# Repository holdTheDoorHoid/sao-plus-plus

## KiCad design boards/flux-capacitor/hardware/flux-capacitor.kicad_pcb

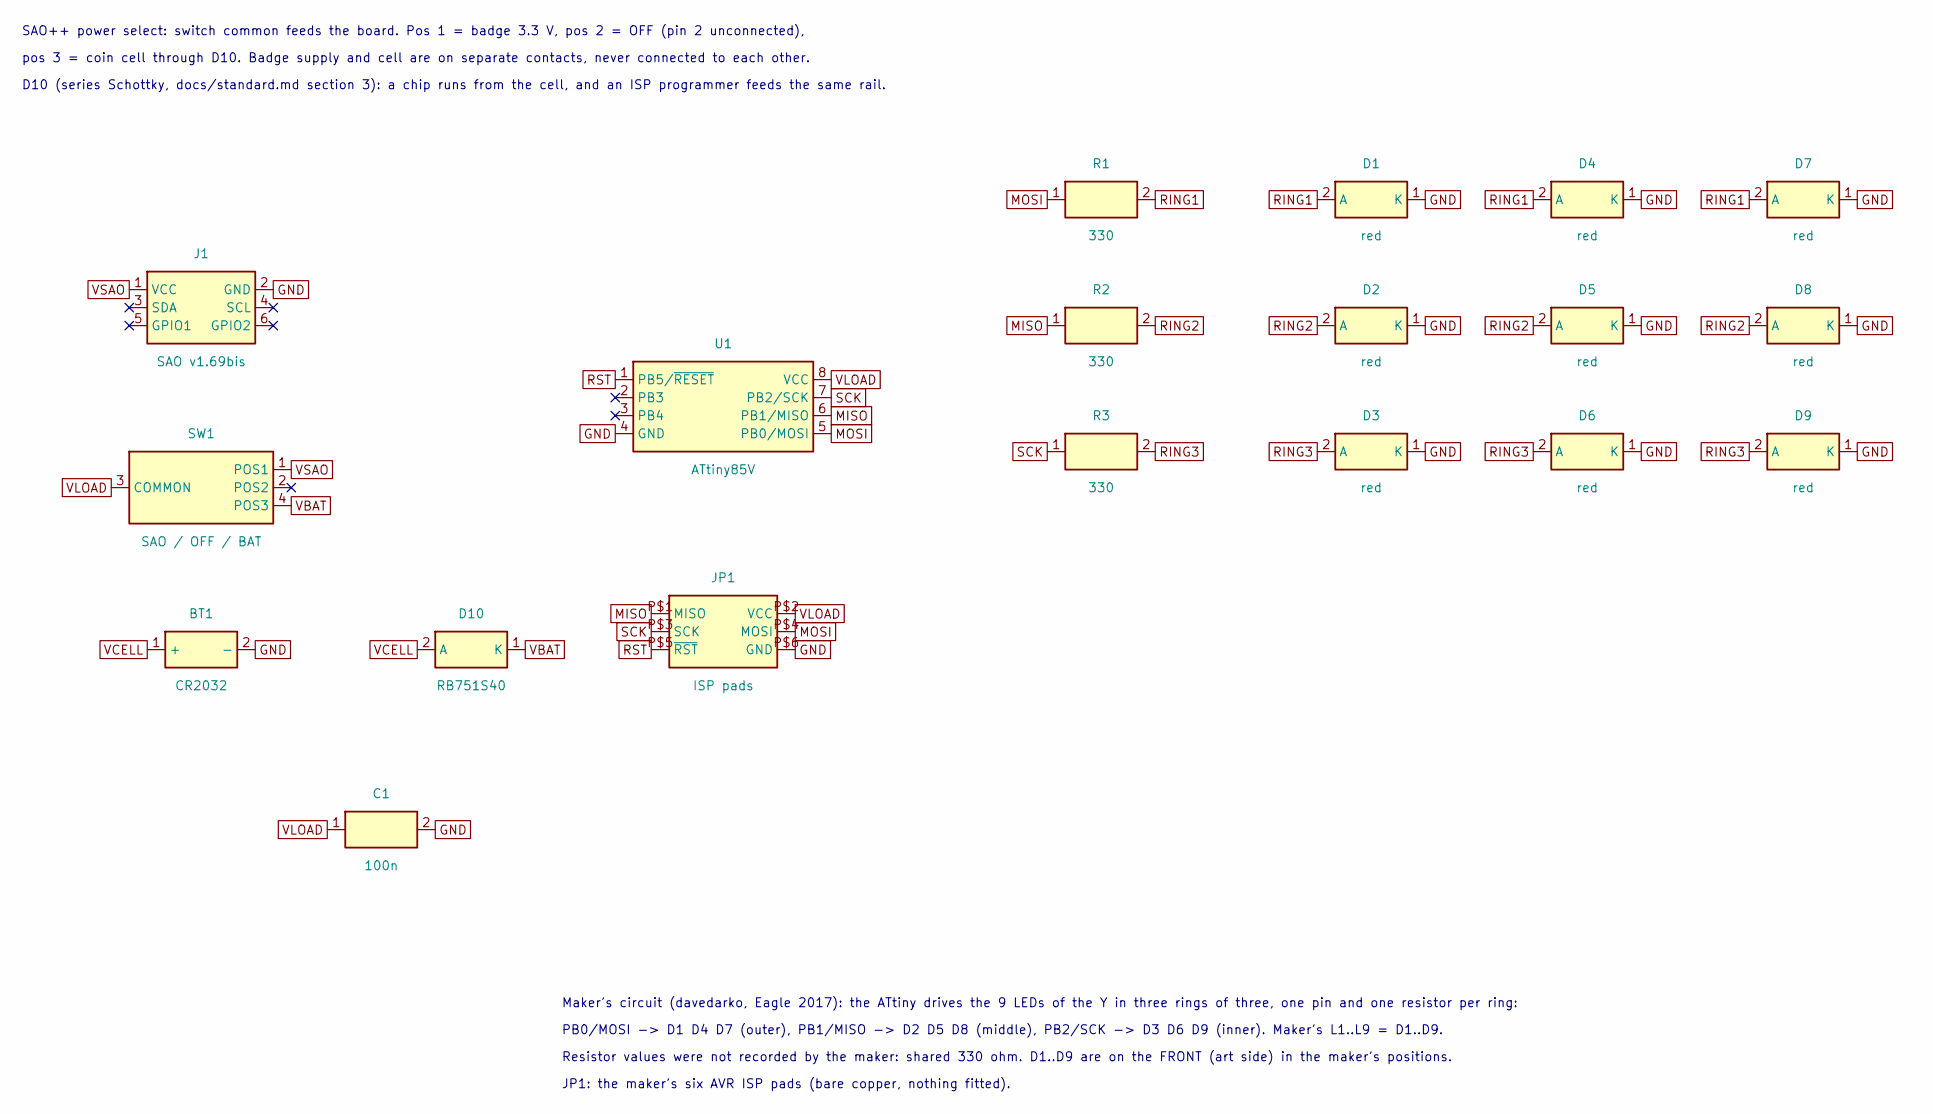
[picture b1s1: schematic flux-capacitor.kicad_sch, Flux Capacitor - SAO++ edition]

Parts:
BT1: CR2032; SAOPP_BAT-01_CR2032_SMD_TE_BAT-HLD-001; MPN BAT-HLD-001; LCSC C7501066
C1: 100n; SAOPP_C_0603_1608Metric; MPN CC0603KRX7R9BB104; LCSC C14663
D1, D2, D3, D4, D5, D6, D7, D8, D9: red; LED_1206_3216Metric; MPN LTST-C150KRKT; LCSC C125086
D10: RB751S40; D_SOD-523; MPN RB751S40T1G; LCSC C232576
J1: SAO v1.69bis; SAOPP_CONN-01_BoxHeader_2x03_P2.54mm_SMD_XFCN_BH254VS-6P; MPN BH254VS-6P; LCSC C492445
JP1: ISP pads; 2X3_SMD_PAD; MPN none: bare pads, nothing fitted
R1, R2, R3: 330; SAOPP_R_0603_1608Metric; MPN 0603WAF3300T5E; LCSC C23138
SW1: SAO / OFF / BAT; SAOPP_SW-01_Slide_SP3T_CK_PCM13SMTR; MPN PCM13SMTR; LCSC C221842
U1: ATtiny85V; SO08-EIAJ; MPN ATTINY85V-10SU; LCSC C152192

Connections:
GND: BT1.2 (-), C1.2, D1.1 (K), D2.1 (K), D3.1 (K), D4.1 (K), D5.1 (K), D6.1 (K), D7.1 (K), D8.1 (K), D9.1 (K), J1.2 (GND), JP1.P$6 (GND), U1.4 (GND)
MISO: JP1.P$1 (MISO), R2.1, U1.6 (PB1/MISO)
MOSI: JP1.P$4 (MOSI), R1.1, U1.5 (PB0/MOSI)
RING1: D1.2 (A), D4.2 (A), D7.2 (A), R1.2
RING2: D2.2 (A), D5.2 (A), D8.2 (A), R2.2
RING3: D3.2 (A), D6.2 (A), D9.2 (A), R3.2
RST: JP1.P$5 (~RST), U1.1 (PB5/~RESET)
SCK: JP1.P$3 (SCK), R3.1, U1.7 (PB2/SCK)
VBAT: D10.1 (K), SW1.4 (POS3)
VCELL: BT1.1 (+), D10.2 (A)
VLOAD: C1.1, JP1.P$2 (VCC), SW1.3 (COMMON), U1.8 (VCC)
VSAO: J1.1 (VCC), SW1.1 (POS1)

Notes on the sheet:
SAO++ power select: switch common feeds the board. Pos 1 = badge 3.3 V, pos 2 = OFF (pin 2 unconnected),
pos 3 = coin cell through D10. Badge supply and cell are on separate contacts, never connected to each other.
D10 (series Schottky, docs/standard.md section 3): a chip runs from the cell, and an ISP programmer feeds the same rail.
Maker's circuit (davedarko, Eagle 2017): the ATtiny drives the 9 LEDs of the Y in three rings of three, one pin and one resistor per ring:
PB0/MOSI -> D1 D4 D7 (outer), PB1/MISO -> D2 D5 D8 (middle), PB2/SCK -> D3 D6 D9 (inner). Maker's L1..L9 = D1..D9.
Resistor values were not recorded by the maker: shared 330 ohm. D1..D9 are on the FRONT (art side) in the maker's positions.
JP1: the maker's six AVR ISP pads (bare copper, nothing fitted).

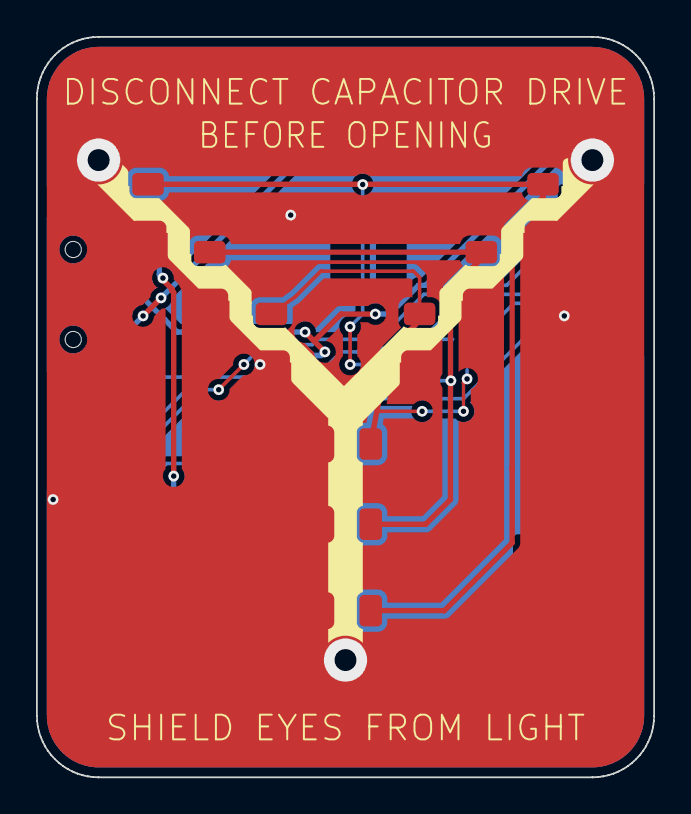
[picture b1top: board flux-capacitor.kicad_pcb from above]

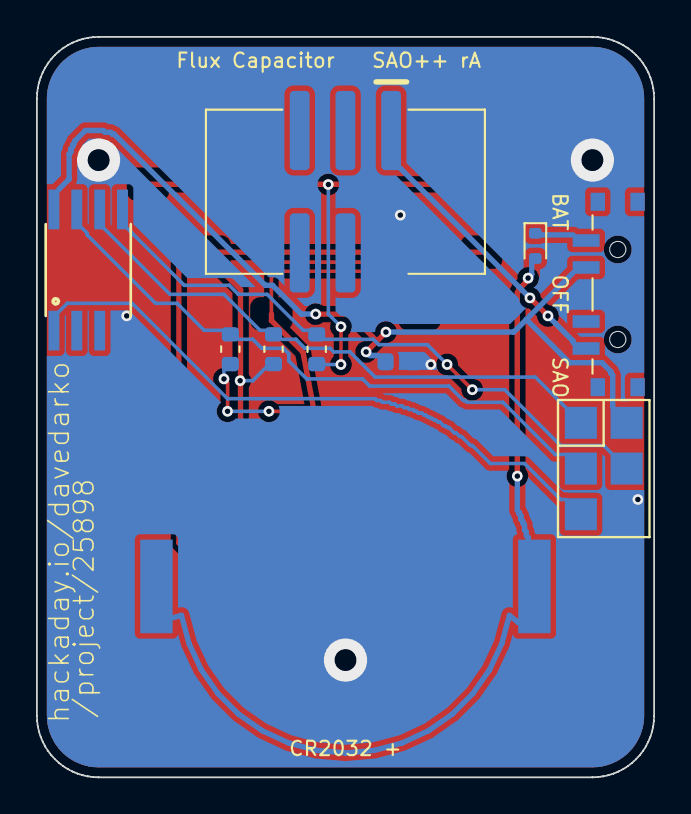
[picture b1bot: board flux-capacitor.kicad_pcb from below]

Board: 2 copper layers, 34.3 x 41.1 mm, 19 parts (10 on the bottom side), 12 nets.

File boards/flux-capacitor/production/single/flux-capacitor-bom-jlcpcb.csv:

Comment,Designator,Footprint,LCSC Part #
CR2032,BT1,SAOPP_BAT-01_CR2032_SMD_TE_BAT-HLD-001,C7501066
100n,C1,SAOPP_C_0603_1608Metric,C14663
red,"D1,D2,D3,D4,D5,D6,D7,D8,D9",LED_1206_3216Metric,C125086
RB751S40,D10,D_SOD-523,C232576
SAO v1.69bis,J1,SAOPP_CONN-01_BoxHeader_2x03_P2.54mm_SMD_XFCN_BH254VS-6P,C492445
ISP pads,JP1,2X3_SMD_PAD,
330,"R1,R2,R3",SAOPP_R_0603_1608Metric,C23138
SAO / OFF / BAT,SW1,SAOPP_SW-01_Slide_SP3T_CK_PCM13SMTR,C221842
ATtiny85V,U1,SO08-EIAJ,C152192

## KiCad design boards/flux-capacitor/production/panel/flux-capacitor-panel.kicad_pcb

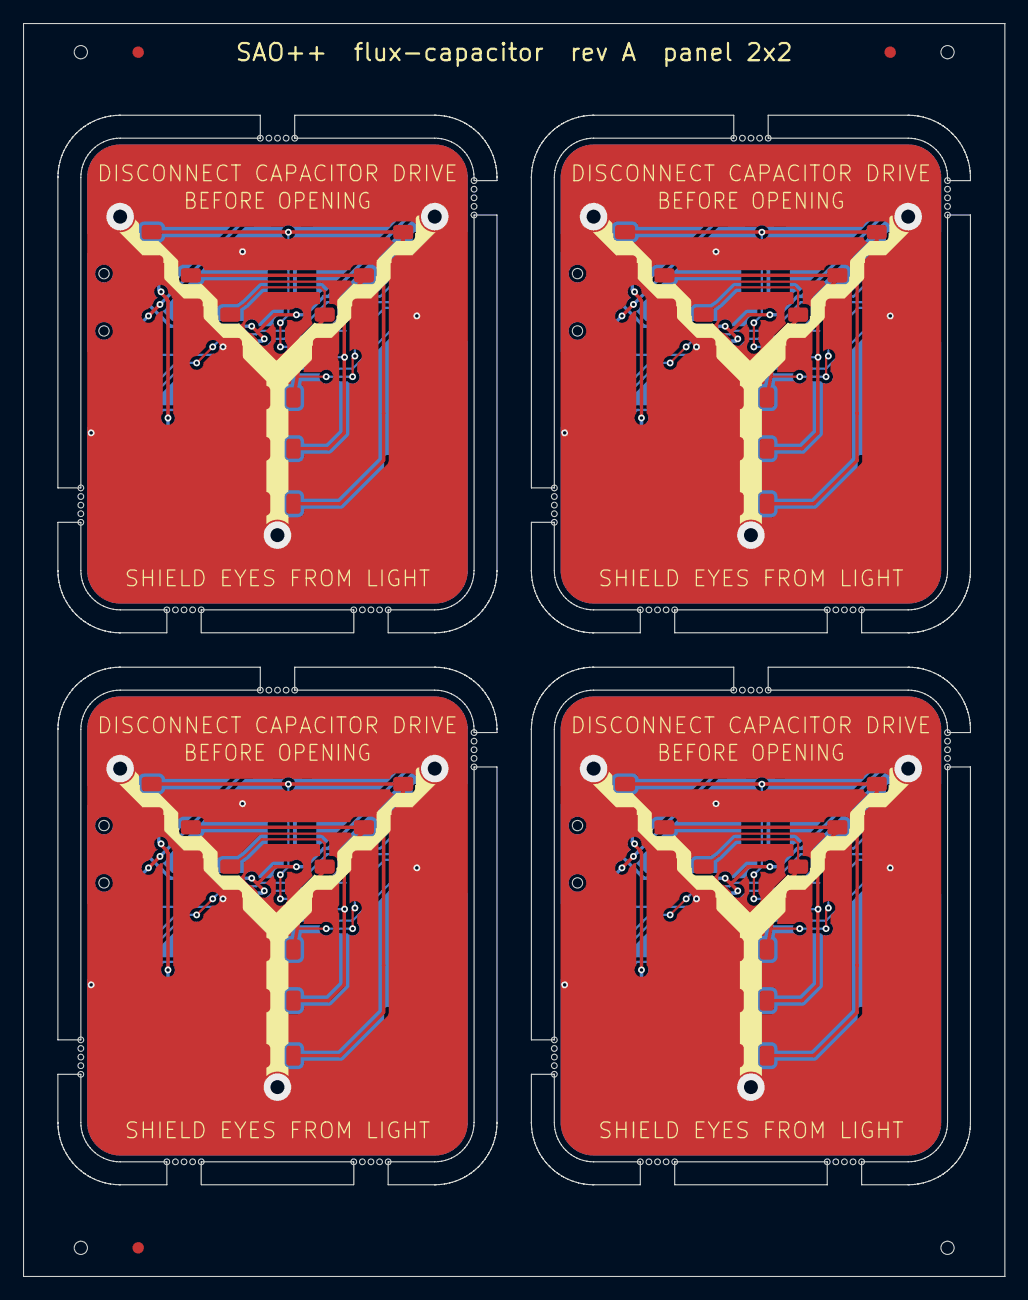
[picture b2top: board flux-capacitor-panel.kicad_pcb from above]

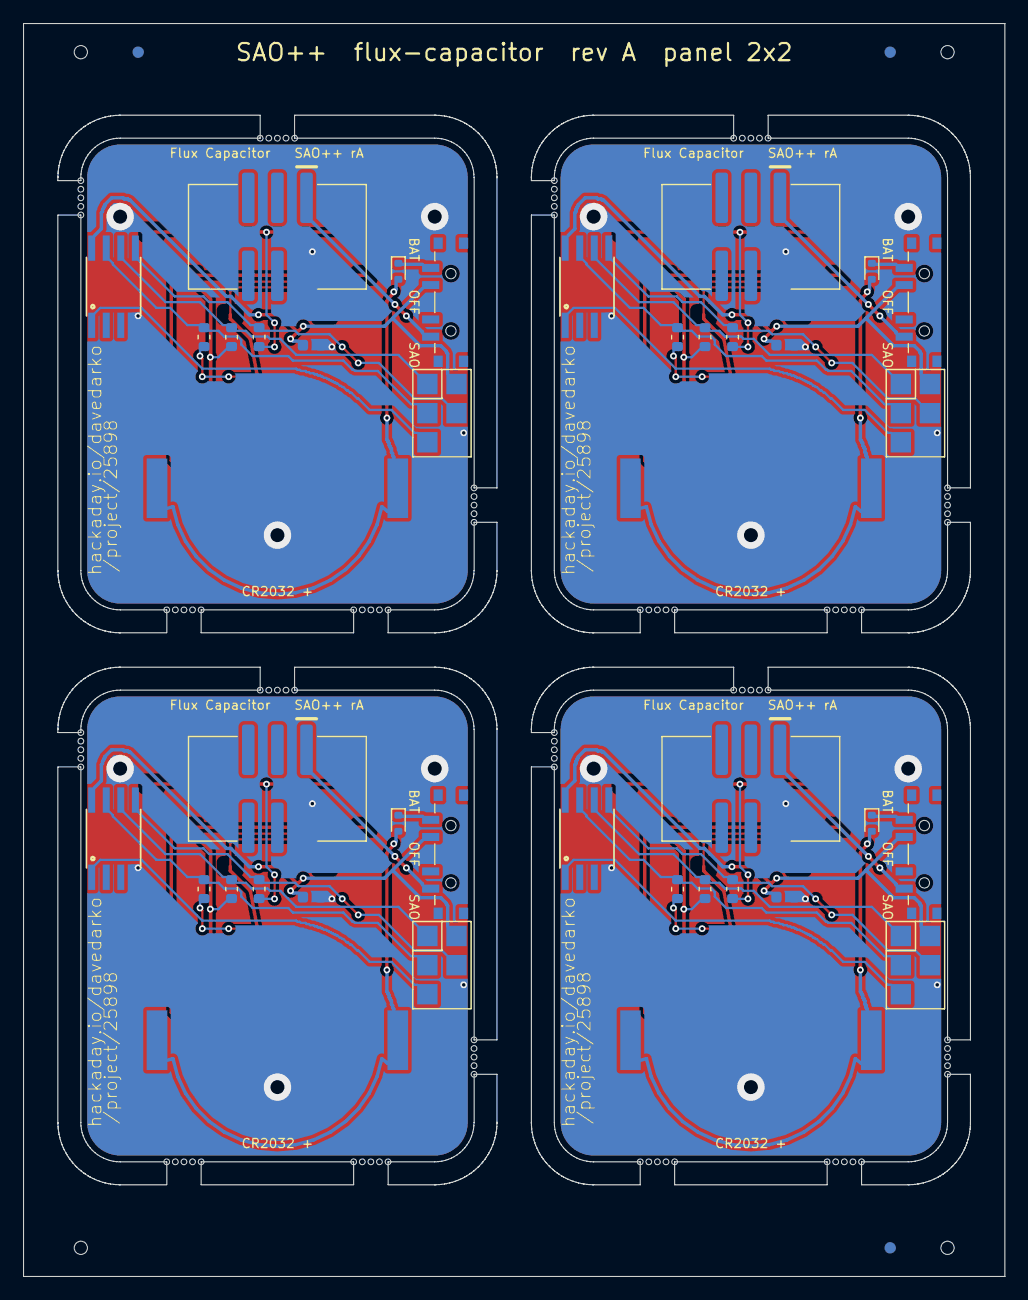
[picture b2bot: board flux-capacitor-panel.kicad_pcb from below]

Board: 2 copper layers, 85.6 x 109.3 mm, 76 parts (40 on the bottom side), 48 nets.

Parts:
BT101, BT201, BT301, BT401: CR2032; SAOPP_BAT-01_CR2032_SMD_TE_BAT-HLD-001
C101, C201, C301, C401: 100n; SAOPP_C_0603_1608Metric
D101, D102, D103, D104, D105, D106, D107, D108, D109, D201, D202, D203, D204, D205, D206, D207, D208, D209, D301, D302, D303, D304, D305, D306, D307, D308, D309, D401, D402, D403, D404, D405, D406, D407, D408, D409: red; LED_1206_3216Metric
D110, D210, D310, D410: RB751S40; D_SOD-523
J101, J201, J301, J401: SAO v1.69bis; SAOPP_CONN-01_BoxHeader_2x03_P2.54mm_SMD_XFCN_BH254VS-6P
JP101, JP201, JP301, JP401: ISP pads; 2X3_SMD_PAD
R101, R102, R103, R201, R202, R203, R301, R302, R303, R401, R402, R403: 330; SAOPP_R_0603_1608Metric
SW101, SW201, SW301, SW401: SAO / OFF / BAT; SAOPP_SW-01_Slide_SP3T_CK_PCM13SMTR
U101, U201, U301, U401: ATtiny85V; SO08-EIAJ

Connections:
B2-GND: BT201.2, C201.2, D201.1, D202.1, D203.1, D204.1, D205.1, D206.1, D207.1, D208.1, D209.1, J201.2, JP201.P$6, U201.4
B2-MISO: JP201.P$1, R202.1, U201.6
B2-MOSI: JP201.P$4, R201.1, U201.5
B2-RING1: D201.2, D204.2, D207.2, R201.2
B2-RING2: D202.2, D205.2, D208.2, R202.2
B2-RING3: D203.2, D206.2, D209.2, R203.2
B2-RST: JP201.P$5, U201.1
B2-SCK: JP201.P$3, R203.1, U201.7
B2-VBAT: D210.1, SW201.4
B2-VCELL: BT201.1, D210.2
B2-VLOAD: C201.1, JP201.P$2, SW201.3, U201.8
B2-VSAO: J201.1, SW201.1
B3-GND: BT301.2, C301.2, D301.1, D302.1, D303.1, D304.1, D305.1, D306.1, D307.1, D308.1, D309.1, J301.2, JP301.P$6, U301.4
B3-MISO: JP301.P$1, R302.1, U301.6
B3-MOSI: JP301.P$4, R301.1, U301.5
B3-RING1: D301.2, D304.2, D307.2, R301.2
B3-RING2: D302.2, D305.2, D308.2, R302.2
B3-RING3: D303.2, D306.2, D309.2, R303.2
B3-RST: JP301.P$5, U301.1
B3-SCK: JP301.P$3, R303.1, U301.7
B3-VBAT: D310.1, SW301.4
B3-VCELL: BT301.1, D310.2
B3-VLOAD: C301.1, JP301.P$2, SW301.3, U301.8
B3-VSAO: J301.1, SW301.1
B4-GND: BT401.2, C401.2, D401.1, D402.1, D403.1, D404.1, D405.1, D406.1, D407.1, D408.1, D409.1, J401.2, JP401.P$6, U401.4
B4-MISO: JP401.P$1, R402.1, U401.6
B4-MOSI: JP401.P$4, R401.1, U401.5
B4-RING1: D401.2, D404.2, D407.2, R401.2
B4-RING2: D402.2, D405.2, D408.2, R402.2
B4-RING3: D403.2, D406.2, D409.2, R403.2
B4-RST: JP401.P$5, U401.1
B4-SCK: JP401.P$3, R403.1, U401.7
B4-VBAT: D410.1, SW401.4
B4-VCELL: BT401.1, D410.2
B4-VLOAD: C401.1, JP401.P$2, SW401.3, U401.8
B4-VSAO: J401.1, SW401.1
GND: BT101.2, C101.2, D101.1, D102.1, D103.1, D104.1, D105.1, D106.1, D107.1, D108.1, D109.1, J101.2, JP101.P$6, U101.4
MISO: JP101.P$1, R102.1, U101.6
MOSI: JP101.P$4, R101.1, U101.5
RING1: D101.2, D104.2, D107.2, R101.2
RING2: D102.2, D105.2, D108.2, R102.2
RING3: D103.2, D106.2, D109.2, R103.2
RST: JP101.P$5, U101.1
SCK: JP101.P$3, R103.1, U101.7
VBAT: D110.1, SW101.4
VCELL: BT101.1, D110.2
VLOAD: C101.1, JP101.P$2, SW101.3, U101.8
VSAO: J101.1, SW101.1

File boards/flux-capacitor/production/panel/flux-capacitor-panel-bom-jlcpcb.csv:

Comment,Designator,Footprint,LCSC Part #
CR2032,"BT101,BT201,BT301,BT401",SAOPP_BAT-01_CR2032_SMD_TE_BAT-HLD-001,C7501066
100n,"C101,C201,C301,C401",SAOPP_C_0603_1608Metric,C14663
red,"D101,D102,D103,D104,D105,D106,D107,D108,D109,D201,D202,D203,D204,D205,D206,D207,D208,D209,D301,D302,D303,D304,D305,D306,D307,D308,D309,D401,D402,D403,D404,D405,D406,D407,D408,D409",LED_1206_3216Metric,C125086
RB751S40,"D110,D210,D310,D410",D_SOD-523,C232576
SAO v1.69bis,"J101,J201,J301,J401",SAOPP_CONN-01_BoxHeader_2x03_P2.54mm_SMD_XFCN_BH254VS-6P,C492445
ISP pads,"JP101,JP201,JP301,JP401",2X3_SMD_PAD,
330,"R101,R102,R103,R201,R202,R203,R301,R302,R303,R401,R402,R403",SAOPP_R_0603_1608Metric,C23138
SAO / OFF / BAT,"SW101,SW201,SW301,SW401",SAOPP_SW-01_Slide_SP3T_CK_PCM13SMTR,C221842
ATtiny85V,"U101,U201,U301,U401",SO08-EIAJ,C152192

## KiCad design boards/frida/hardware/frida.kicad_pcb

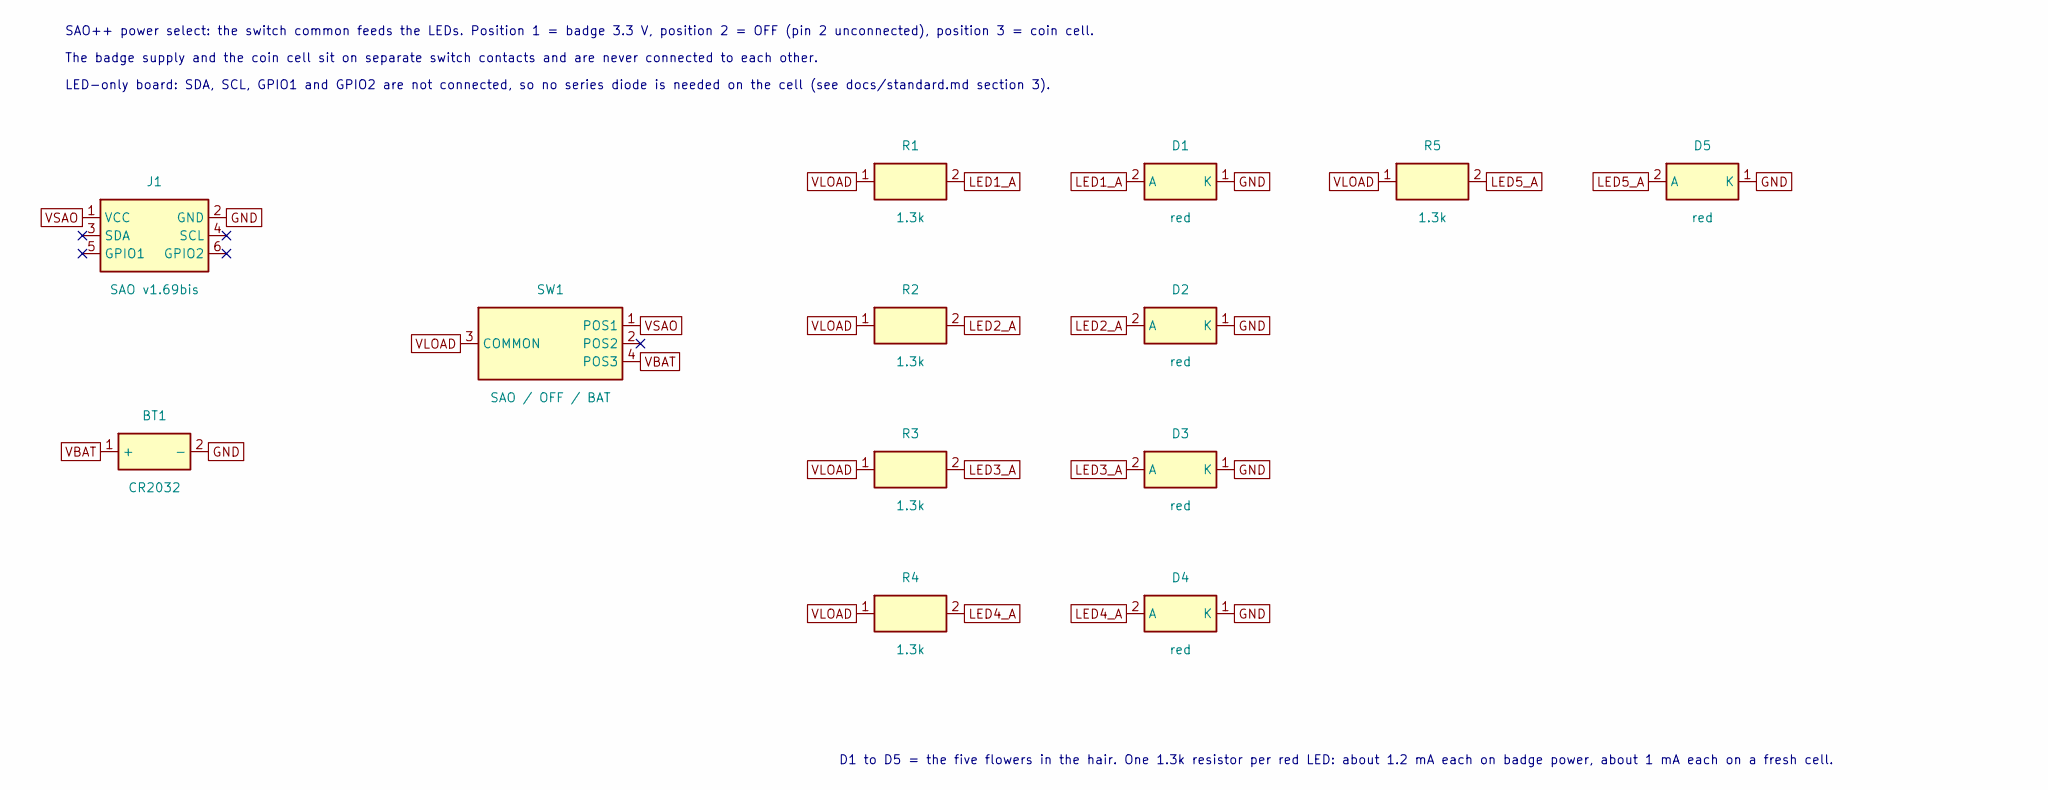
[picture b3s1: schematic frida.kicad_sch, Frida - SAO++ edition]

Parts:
BT1: CR2032; SAOPP_BAT-01_CR2032_SMD_TE_BAT-HLD-001; MPN BAT-HLD-001; LCSC C7501066
D1, D2, D3, D4, D5: red; SAOPP_LED-10_1206_ReverseMount_ThroughBoard; MPN LTST-C230KRKT; LCSC C125107
J1: SAO v1.69bis; SAOPP_CONN-01_BoxHeader_2x03_P2.54mm_SMD_XFCN_BH254VS-6P; MPN BH254VS-6P; LCSC C492445
R1, R2, R3, R4, R5: 1.3k; SAOPP_R_0603_1608Metric; MPN 0603WAF1301T5E; LCSC C22767
SW1: SAO / OFF / BAT; SAOPP_SW-01_Slide_SP3T_CK_PCM13SMTR; MPN PCM13SMTR; LCSC C221842

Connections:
GND: BT1.2 (-), D1.1 (K), D2.1 (K), D3.1 (K), D4.1 (K), D5.1 (K), J1.2 (GND)
LED1_A: D1.2 (A), R1.2
LED2_A: D2.2 (A), R2.2
LED3_A: D3.2 (A), R3.2
LED4_A: D4.2 (A), R4.2
LED5_A: D5.2 (A), R5.2
VBAT: BT1.1 (+), SW1.4 (POS3)
VLOAD: R1.1, R2.1, R3.1, R4.1, R5.1, SW1.3 (COMMON)
VSAO: J1.1 (VCC), SW1.1 (POS1)

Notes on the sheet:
SAO++ power select: the switch common feeds the LEDs. Position 1 = badge 3.3 V, position 2 = OFF (pin 2 unconnected), position 3 = coin cell.
The badge supply and the coin cell sit on separate switch contacts and are never connected to each other.
LED-only board: SDA, SCL, GPIO1 and GPIO2 are not connected, so no series diode is needed on the cell (see docs/standard.md section 3).
D1 to D5 = the five flowers in the hair. One 1.3k resistor per red LED: about 1.2 mA each on badge power, about 1 mA each on a fresh cell.

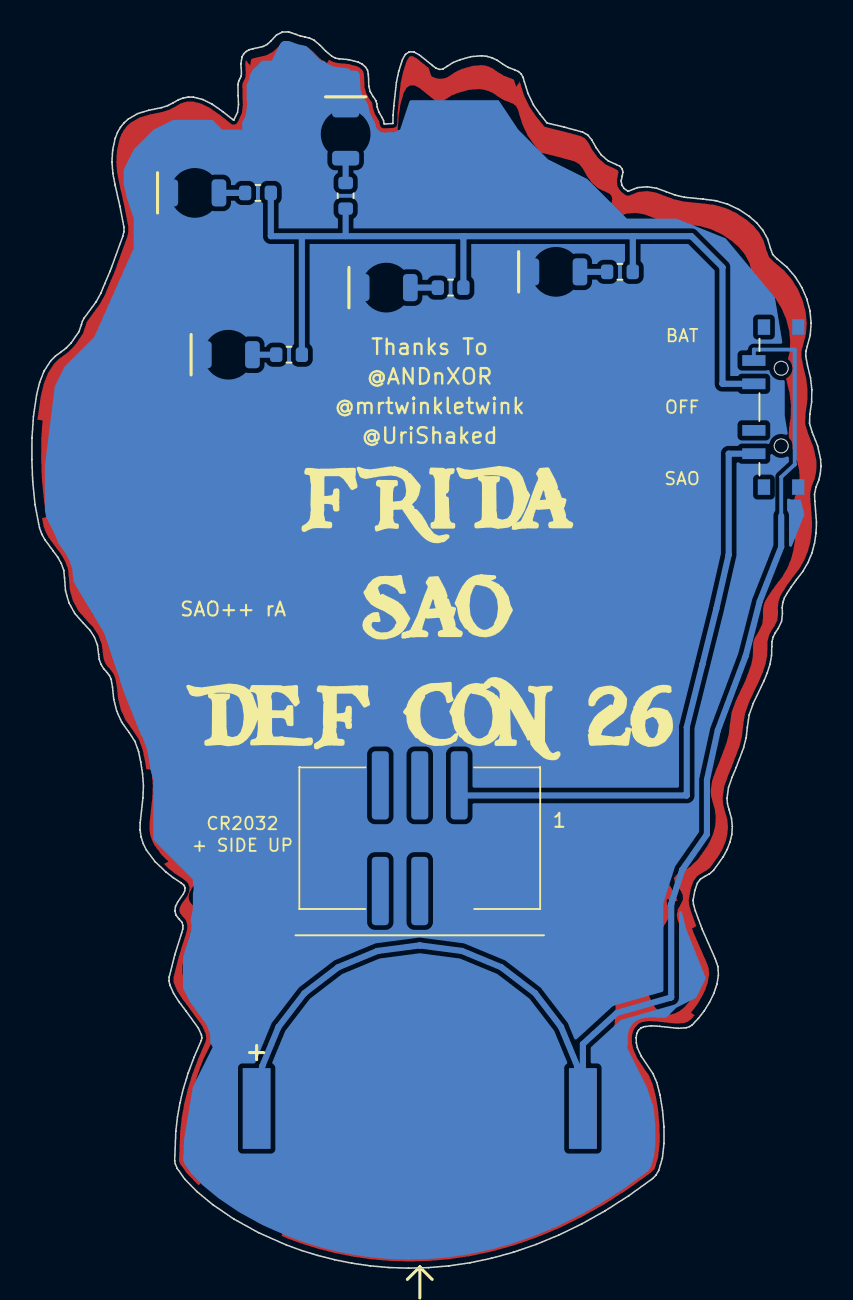
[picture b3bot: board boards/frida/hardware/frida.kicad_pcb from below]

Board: 2 copper layers, 50.8 x 79.6 mm, 15 parts (14 on the bottom side), 9 nets.

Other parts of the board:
svg2mod: G***; frida
svg2mod#2: G***; fridaback

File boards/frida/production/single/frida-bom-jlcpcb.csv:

Comment,Designator,Footprint,LCSC Part #
CR2032,BT1,SAOPP_BAT-01_CR2032_SMD_TE_BAT-HLD-001,C7501066
red,"D1,D2,D3,D4,D5",SAOPP_LED-10_1206_ReverseMount_ThroughBoard,C125107
SAO v1.69bis,J1,SAOPP_CONN-01_BoxHeader_2x03_P2.54mm_SMD_XFCN_BH254VS-6P,C492445
1.3k,"R1,R2,R3,R4,R5",SAOPP_R_0603_1608Metric,C22767
SAO / OFF / BAT,SW1,SAOPP_SW-01_Slide_SP3T_CK_PCM13SMTR,C221842

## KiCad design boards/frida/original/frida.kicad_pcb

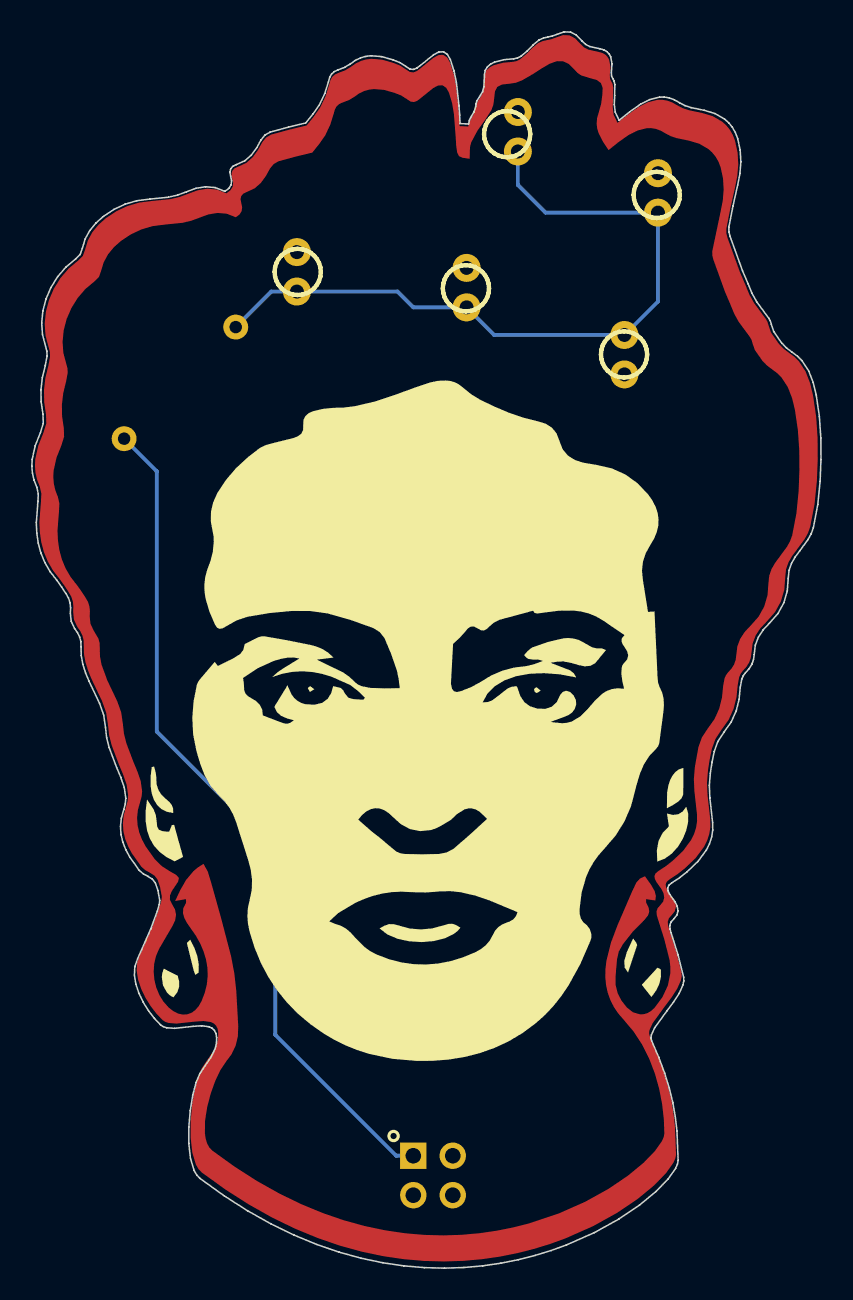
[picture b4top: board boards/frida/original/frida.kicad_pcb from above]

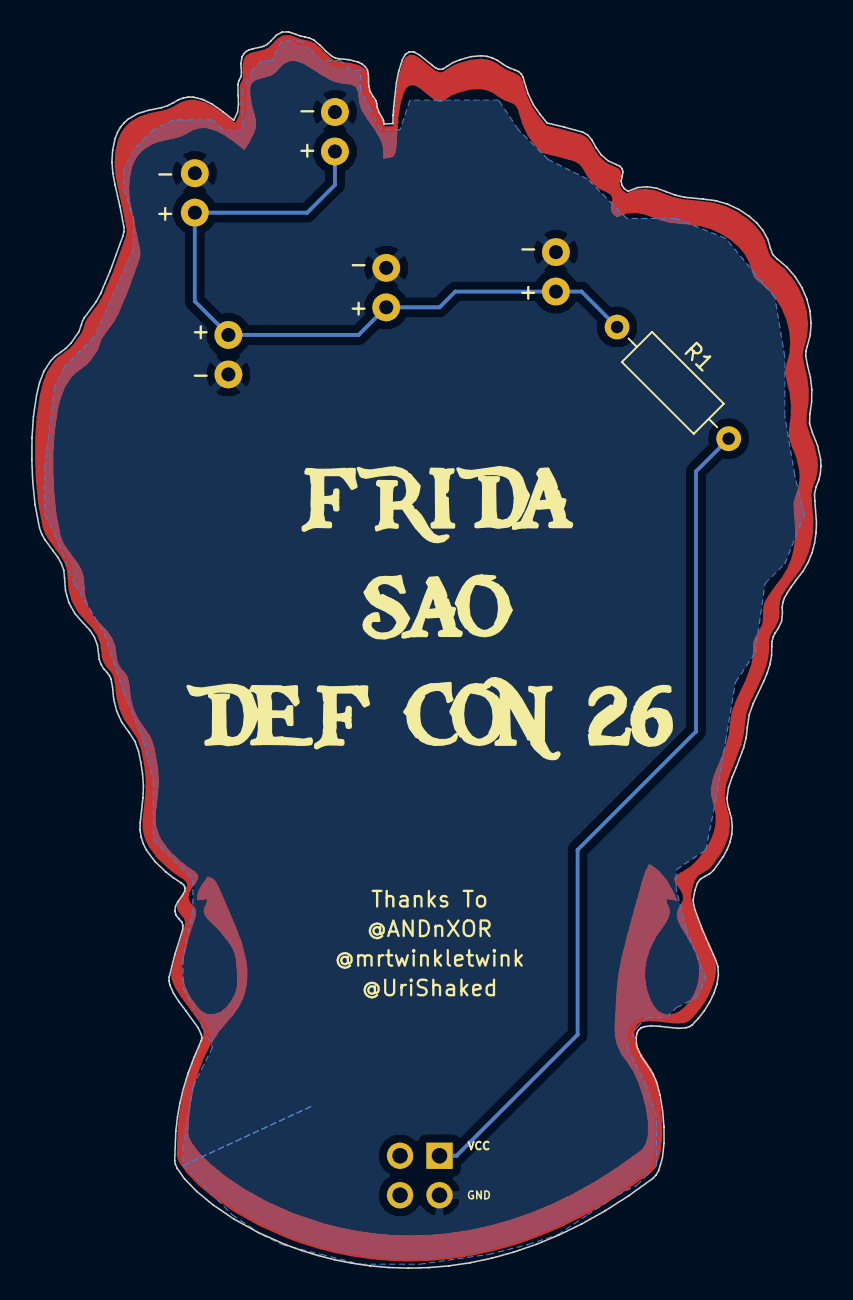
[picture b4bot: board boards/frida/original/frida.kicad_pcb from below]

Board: 2 copper layers, 50.8 x 79.6 mm, 9 parts (8 on the bottom side), 3 nets.

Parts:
D1, D2, D3, D4, D5: LED; LED_D3.0mm_FlatTop_edit
J1: Conn_02x02_Odd_Even; PinHeader_2x02_P2.54mm_Vertical_edit
R1: R; R_Axial_DIN0207_L6.3mm_D2.5mm_P10.16mm_Horizontal
svg2mod: G***; frida
svg2mod#2: G***; fridaback

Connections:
unnamed: D1.1, D2.1, D3.1, D4.1, D5.1, J1.3
unnamed: D1.2, D2.2, D3.2, D4.2, D5.2, R1.1
unnamed: J1.1, R1.2

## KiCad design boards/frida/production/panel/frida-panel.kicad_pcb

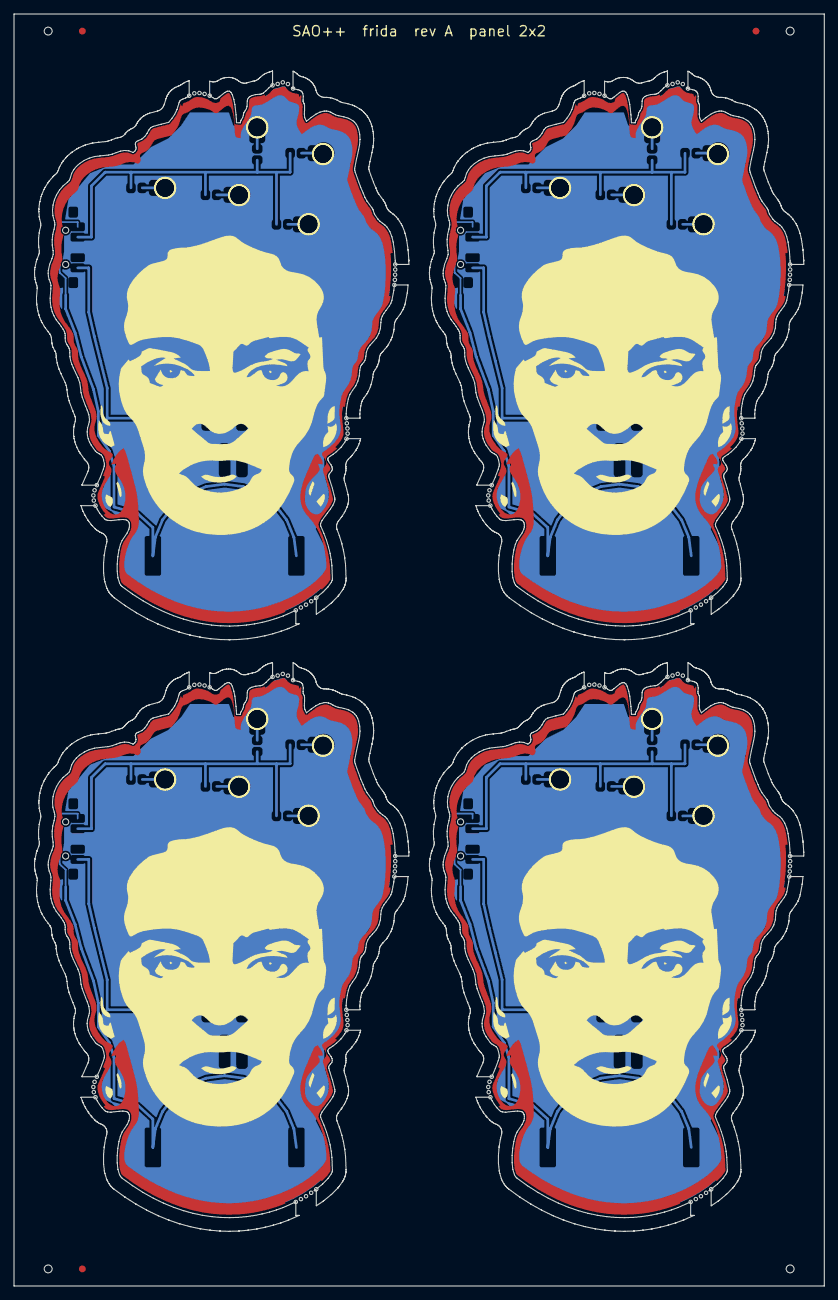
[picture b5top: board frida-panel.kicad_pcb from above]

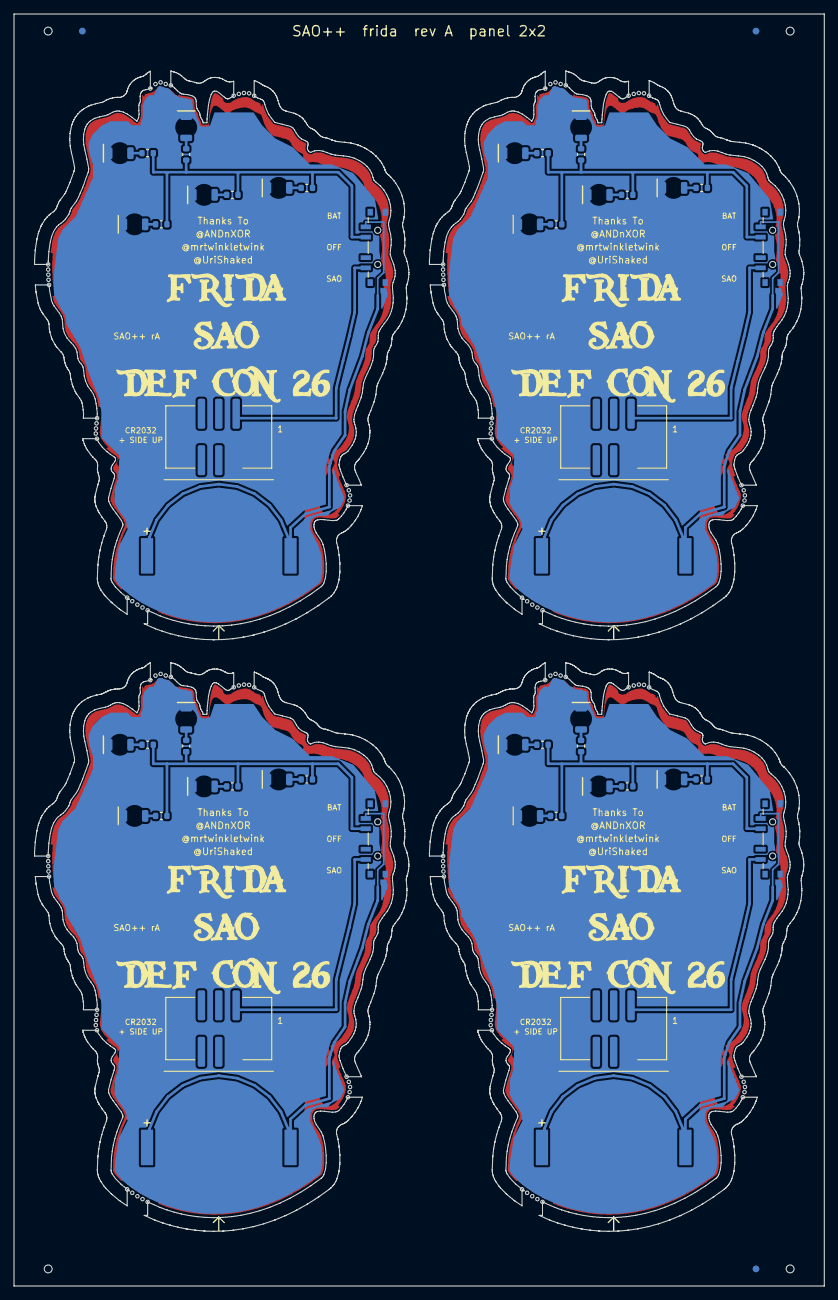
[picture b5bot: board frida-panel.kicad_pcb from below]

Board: 2 copper layers, 118.6 x 186.2 mm, 60 parts (56 on the bottom side), 36 nets.

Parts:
BT101, BT201, BT301, BT401: CR2032; SAOPP_BAT-01_CR2032_SMD_TE_BAT-HLD-001
D101, D102, D103, D104, D105, D201, D202, D203, D204, D205, D301, D302, D303, D304, D305, D401, D402, D403, D404, D405: red; SAOPP_LED-10_1206_ReverseMount_ThroughBoard
J101, J201, J301, J401: SAO v1.69bis; SAOPP_CONN-01_BoxHeader_2x03_P2.54mm_SMD_XFCN_BH254VS-6P
R101, R102, R103, R104, R105, R201, R202, R203, R204, R205, R301, R302, R303, R304, R305, R401, R402, R403, R404, R405: 1.3k; SAOPP_R_0603_1608Metric
SW101, SW201, SW301, SW401: SAO / OFF / BAT; SAOPP_SW-01_Slide_SP3T_CK_PCM13SMTR
svg2mod, svg2mod#2, svg2mod#3, svg2mod#4: G***; frida
svg2mod#5, svg2mod#6, svg2mod#7, svg2mod#8: G***; fridaback

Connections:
B2-GND: BT201.2, D201.1, D202.1, D203.1, D204.1, D205.1, J201.2
B2-LED1_A: D201.2, R201.2
B2-LED2_A: D202.2, R202.2
B2-LED3_A: D203.2, R203.2
B2-LED4_A: D204.2, R204.2
B2-LED5_A: D205.2, R205.2
B2-VBAT: BT201.1, SW201.4
B2-VLOAD: R201.1, R202.1, R203.1, R204.1, R205.1, SW201.3
B2-VSAO: J201.1, SW201.1
B3-GND: BT301.2, D301.1, D302.1, D303.1, D304.1, D305.1, J301.2
B3-LED1_A: D301.2, R301.2
B3-LED2_A: D302.2, R302.2
B3-LED3_A: D303.2, R303.2
B3-LED4_A: D304.2, R304.2
B3-LED5_A: D305.2, R305.2
B3-VBAT: BT301.1, SW301.4
B3-VLOAD: R301.1, R302.1, R303.1, R304.1, R305.1, SW301.3
B3-VSAO: J301.1, SW301.1
B4-GND: BT401.2, D401.1, D402.1, D403.1, D404.1, D405.1, J401.2
B4-LED1_A: D401.2, R401.2
B4-LED2_A: D402.2, R402.2
B4-LED3_A: D403.2, R403.2
B4-LED4_A: D404.2, R404.2
B4-LED5_A: D405.2, R405.2
B4-VBAT: BT401.1, SW401.4
B4-VLOAD: R401.1, R402.1, R403.1, R404.1, R405.1, SW401.3
B4-VSAO: J401.1, SW401.1
GND: BT101.2, D101.1, D102.1, D103.1, D104.1, D105.1, J101.2
LED1_A: D101.2, R101.2
LED2_A: D102.2, R102.2
LED3_A: D103.2, R103.2
LED4_A: D104.2, R104.2
LED5_A: D105.2, R105.2
VBAT: BT101.1, SW101.4
VLOAD: R101.1, R102.1, R103.1, R104.1, R105.1, SW101.3
VSAO: J101.1, SW101.1

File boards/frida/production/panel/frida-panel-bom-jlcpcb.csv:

Comment,Designator,Footprint,LCSC Part #
CR2032,"BT101,BT201,BT301,BT401",SAOPP_BAT-01_CR2032_SMD_TE_BAT-HLD-001,C7501066
red,"D101,D102,D103,D104,D105,D201,D202,D203,D204,D205,D301,D302,D303,D304,D305,D401,D402,D403,D404,D405",SAOPP_LED-10_1206_ReverseMount_ThroughBoard,C125107
SAO v1.69bis,"J101,J201,J301,J401",SAOPP_CONN-01_BoxHeader_2x03_P2.54mm_SMD_XFCN_BH254VS-6P,C492445
1.3k,"R101,R102,R103,R104,R105,R201,R202,R203,R204,R205,R301,R302,R303,R304,R305,R401,R402,R403,R404,R405",SAOPP_R_0603_1608Metric,C22767
SAO / OFF / BAT,"SW101,SW201,SW301,SW401",SAOPP_SW-01_Slide_SP3T_CK_PCM13SMTR,C221842
